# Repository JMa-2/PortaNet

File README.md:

# ***PortaNet Guide***
---
## *TABLE OF CONTENTS*
- [Introduction](#introduction)
- [Hardware](#hardware)
    - [Hardware General](#hardware-general)
    - [Hardware Tools](#hardware-tools)
    - [Schematic](#schematic)
    - [PCB Layout](#pcb-layout)
    - [BOM](#bom)
- [Software](#software)
    - [Software General](#software-general)
    - [Software Tools](#software-tools)
    - [Architecture](#architecture)
    - [Building](#building--flashing)
- [How to Use](#how-to-use)
    - [Use General](#use-general)
    - [PuTTy](#putty)
    - [Console Commands](#console-commands)
<br>
<br>
<br>

## *INTRODUCTION*
The PortaNet is a wifi access point (AP) using the Espressif ESP32-C3FH4 microcontroller. The PortaNet holds the shape and connection types of a typical USB stick. The AP's settings can be modified via a serial console. At this point PuTTy is the only tested terminal emulator software for use with PortaNet.

<br>

<br>
<br>
<br>

## *HARDWARE*
### Hardware General
The critical component consists of the [Espressif ESP32-C3FH4](https://www.espressif.com/en/products/socs/esp32-c3). The ESP32-C3FH4 microcontroller is a ESP32-C3 variant with 4MB internal flash. Simply buying the "normal" ESP32-C3 variant will not suffice due to the lack of internal flash.

The design utilizes a 50 &Omega; impedance, 2.4 GHz wifi antenna. Antennas such as [this](https://www.amazon.com/gp/product/B07D1Z3W7T/ref=ppx_yo_dt_b_search_asin_title?ie=UTF8&psc=1) and [this](https://www.amazon.com/gp/product/B0991PKTDL/ref=ppx_yo_dt_b_search_asin_title?ie=UTF8&psc=1) have worked successfully. There is an unused &pi;-matching circuit that could aid in supporting other antennas.

### Hardware Tools
KiCad v6 was utilized as the EDA tool. The KiCad project can be found in the [hardware directory](hardware/kicad/PortaNet/). Additionally my [KiCad Library](http://192.168.1.19:3000/JMa/KiCad_Library) may contain needed symbols and footprints that the project references.

### Schematic
The current schematic can be seen [here](hardware/kicad/PortaNet_SCH.pdf). 

On page 2 of the schematic, the only oddity worth explaining is the NC of C2. Having C2 installed results in the GPIO9 (pin 15) being pulled low. Resulting in the firmware getting stuck in the bootloader.

On page 3 of the schematic, lives the unused &pi;-matching circuit labeled `Antenna`. If the &pi;-matching circuit does not want to be used, then `L1` should be shorted with a 0 &Omega; resistor.

On page 3 also lives the `Crystal` section. While the load capacitors are labeled 7pF, 8pF caps work with no issues thus far. 

### PCB Layout
The board layout consists of 4 layers, with components on both the top and bottom layers. 

The layer structure consists of the top layer being a signal layer, the second and third layer being GND layers, and the bottom layer being a PWR/signal layer. The top layer or layer 1 of the board is structured to isolate noise sources from other hardware sections. The sub-circuits on the top layer are split into PWR/USB, microcontroller (uC), crystal (XTAL), and radio frequency (RF) sections. GND traces with vias surround the RF and XTAL sections of the top layer.

### BOM
The BOM can be found [here](hardware/kicad/PortaNet/PortaNet.csv). As well as a copy and paste is below. It is again important to note that **the ESP32-C3 part purchased must be a part that contains internal flash.**

| Ref               | Qnty | Value            | Cmp name         | Footprint                                                       |
|-------------------|------|------------------|------------------|-----------------------------------------------------------------|
| C1,               | 1    | 1uF              | C_Small          | Capacitor_SMD:C_0603_1608Metric                                 |
| C2,               | 1    | NC               | C_Small          | Capacitor_SMD:C_0603_1608Metric                                 |
| C3, C7, C13,      | 3    | 0.1uF            | C_Small          | Capacitor_SMD:C_0603_1608Metric                                 |
| C4, C8, C10, C14, | 4    | 10uF             | C_Small          | Capacitor_SMD:C_0603_1608Metric                                 |
| C5, C6,           | 2    | TBD              | C_Small          | Capacitor_SMD:C_0603_1608Metric                                 |
| C9,               | 1    | .1uF             | C_Small          | Capacitor_SMD:C_0603_1608Metric                                 |
| C11, C12,         | 2    | 7pF              | C_Small          | Capacitor_SMD:C_0603_1608Metric                                 |
| D1,               | 1    | DSS13UTR         | D_Schottky       | Diode_SMD:D_SOD-123F                                            |
| J1,               | 1    | SMA              | Conn_Coaxial     | Connector_Coaxial:SMA_Amphenol_132134_Vertical                  |
| J2,               | 1    | Molex 0480370001 | USB_A            | JoesFootprints:Molex_0480370001                                 |
| L1,               | 1    | TBD              | L                | Inductor_SMD:L_0805_2012Metric_Pad1.15x1.40mm_HandSolder        |
| R1, R2, R3,       | 3    | 10k              | R_Small_US       | Resistor_SMD:R_0805_2012Metric                                  |
| R4, R5,           | 2    | 22               | R_Small_US       | Resistor_SMD:R_0805_2012Metric                                  |
| SW1,              | 1    | 434133025816     | SW_SPST          | Button_Switch_SMD:SW_Push_1P1T_NO_Vertical_Wuerth_434133025816  |
| U1,               | 1    | ESP32-C3         | ESP32-C3         | Package_DFN_QFN:QFN-32-1EP_5x5mm_P0.5mm_EP3.3x3.3mm_ThermalVias |
| U2,               | 1    | AP2114HA-3.3TRG1 | AP2114HA-3.3TRG1 | Package_TO_SOT_SMD:SOT-223-3_TabPin2                            |
| Y1,               | 1    | FL400WFQA1       | Crystal_GND24    | Crystal:Crystal_SMD_3225-4Pin_3.2x2.5mm                         |

<br>
<br>
<br>

## *SOFTWARE*
### Software General
The firmware is written in C using [Espressif's IOT Development Framework (ESP-IDF)](https://www.espressif.com/en/products/sdks/esp-idf#:~:text=ESP%2DIDF%20is%20Espressif's%20official,as%20C%20and%20C%2B%2B.). The software utilizes [FreeRTOS](https://www.freertos.org/) as part of the ESP-IDF as well. 

### Software Tools
The software used `ESP-IDF v5.0-dev-3032-g7e71c0cff2-dirty`. The ESP-IDF can be found [here](https://github.com/espressif/esp-idf).

### Architecture
The software utilizes an RTOS variation of [A JcM Architecture](http://192.168.1.19:3000/JMa/JcmArch). Architecture formats can be seen [here](firmware/)

Two threads exists in the software. The first thread, which has the highest priority, is the `Access Point Thread`. The second thread, which has a lower priority compared to the `Access Point Thread`, is the `Console Thread`. The `Access Point Thread` is controlling the wifi soft-AP and the `Console Thread` is controlling the serial console processes that make requests to the `Access Point Interface`. 

### Building & Flashing
1. Clone the repo<br>
`git clone http://192.168.1.19:3000/JMa/PortaNet.git`

2. Enter the firmware folder<br>
`cd PortaNet/firmware/PortaNet/`

3. Source the ESP-IDF export script from proper location<br>
example: `. ~/esp-idf/export.sh`

4. Ensure the target is set to the ESP32-C3<br>
`idf.py set-target esp32c3`

5. Build the project<br>
`idf.py build`

6. Flash the device<br>
`idf.py -p PORT flash`

<br>

If issues arise, Espressif has good documentation located [here](https://docs.espressif.com/projects/esp-idf/en/latest/esp32c3/get-started/linux-macos-setup.html).

<br>
<br>
<br>

## *HOW TO USE*
### Use General
Since the device uses USB 2.0, the operating voltage is 5V. Typical PC USB receptacles work just fine and even phone/device charging bricks should work without issue. The device draws less that 100mA so there shouldn't be power rating issues to monitor.

### PuTTy
At this point, PuTTy is the only terminal emulator that the device has really been tested with. PicoCom, the linux utility, appears to work as well.

PuTTy can be downloaded from [here](https://www.putty.org/) and it is widely used enough to easily find tutorials via Google or Youtube. 

### Console Commands
`help`<br>
Print the list of registered commands.

`status`<br>
Status of the AP which includes info such as the SSID, password, max number of connections, and wifi channel.

`reset`<br>
Reset the AP to its default credentials

`on`<br>
Turn on the AP.

`off`<br>
Turn off the AP.

`devices`<br>
Show info on currently connected devices.

`ssid <NAME>`<br>
Request new SSID of AP.

`password <PW>`<br>
Request new password of AP.

`maxconn <#>`<br>
Request new number of max connection of the AP.

`restart`<br>
Request the AP to restart.

`version`<br>
Request the current software version.

`channel <#>`<br>
Request new wifi channel of the AP.

<br>
<br>
<br>

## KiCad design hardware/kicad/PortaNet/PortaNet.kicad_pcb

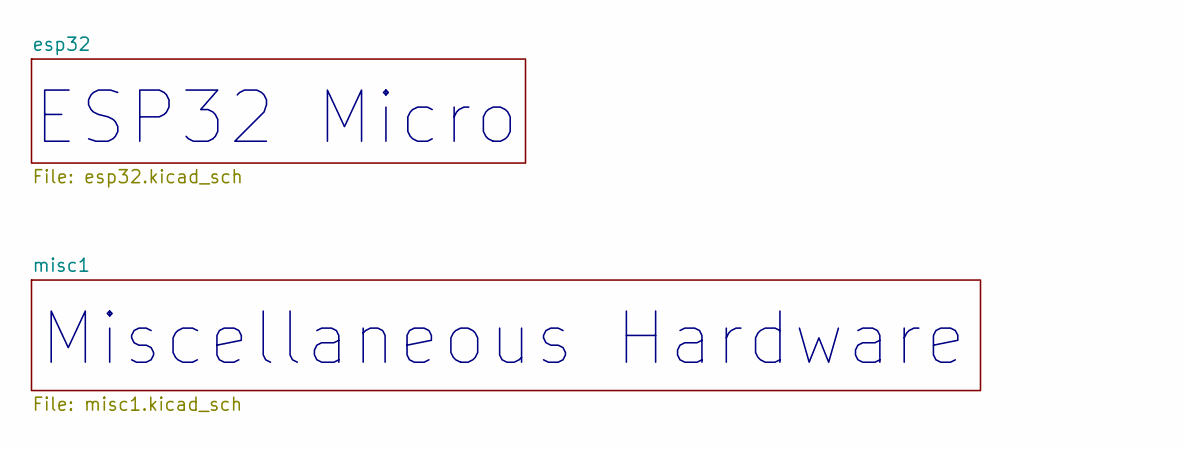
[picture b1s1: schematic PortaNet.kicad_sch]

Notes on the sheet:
Miscellaneous Hardware
ESP32 Micro

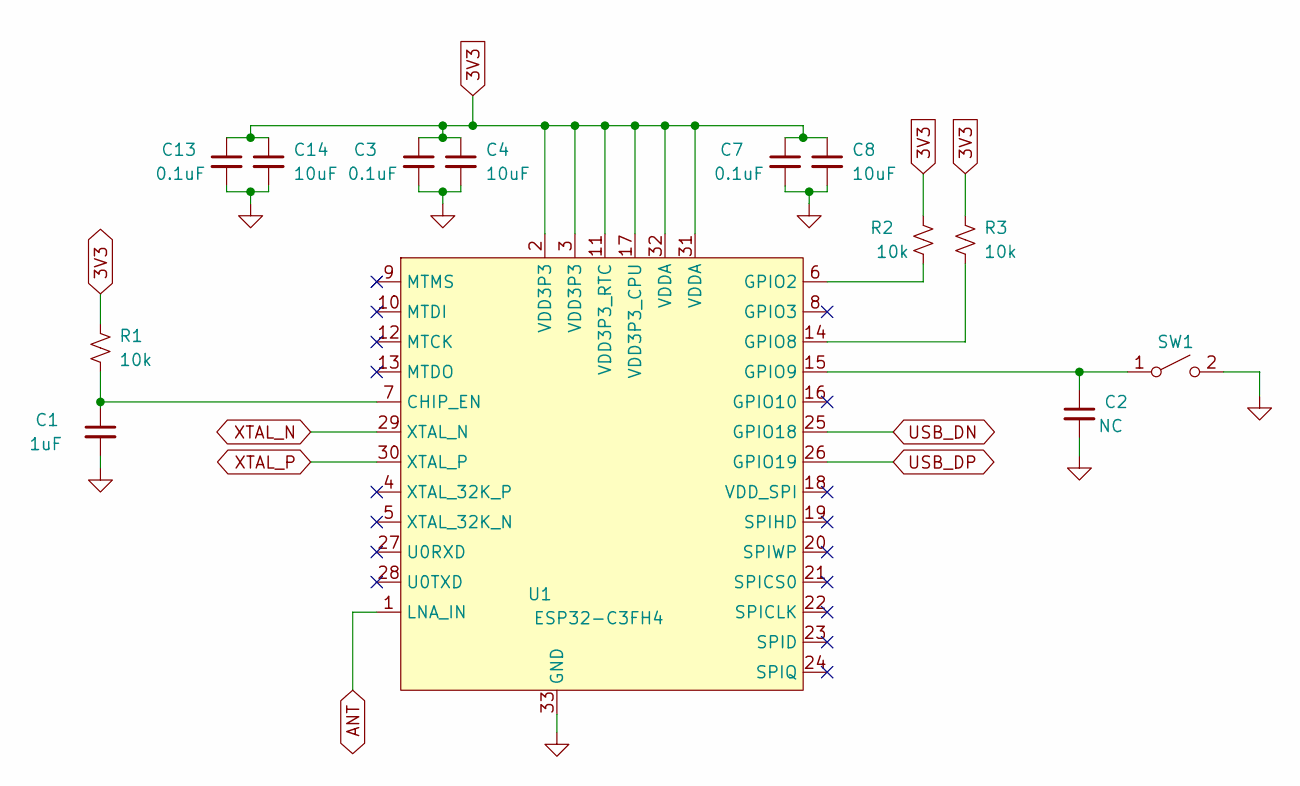
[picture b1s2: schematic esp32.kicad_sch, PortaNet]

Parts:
C1: 1uF; C_0603_1608Metric
C2: NC; C_0603_1608Metric
C3, C7, C13: 0.1uF; C_0603_1608Metric
C4, C8, C14: 10uF; C_0603_1608Metric
R1, R2, R3: 10k; R_0805_2012Metric
SW1: 434133025816; SW_Push_1P1T_NO_Vertical_Wuerth_434133025816
U1: ESP32-C3FH4; QFN-32-1EP_5x5mm_P0.5mm_EP3.3x3.3mm_ThermalVias

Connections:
3V3: C3.1, C4.1, C7.1, C8.1, C13.1, C14.1, R1.2, R2.2, R3.2, U1.2 (VDD3P3), U1.3 (VDD3P3), U1.11 (VDD3P3_RTC), U1.17 (VDD3P3_CPU), U1.31 (VDDA), U1.32 (VDDA); also elsewhere on the board
ANT: U1.1 (LNA_IN); also elsewhere on the board
GND: C1.2, C2.2, C3.2, C4.2, C7.2, C8.2, C13.2, C14.2, SW1.2 (B), U1.33 (GND); also elsewhere on the board
unnamed: C1.1, R1.1, U1.7 (CHIP_EN)
unnamed: C2.1, SW1.1 (A), U1.15 (GPIO9)
unnamed: R3.1, U1.14 (GPIO8)
unnamed: R2.1, U1.6 (GPIO2)
USB_DN: U1.25 (GPIO18); also elsewhere on the board
USB_DP: U1.26 (GPIO19); also elsewhere on the board
XTAL_N: U1.29 (XTAL_N); also elsewhere on the board
XTAL_P: U1.30 (XTAL_P); also elsewhere on the board

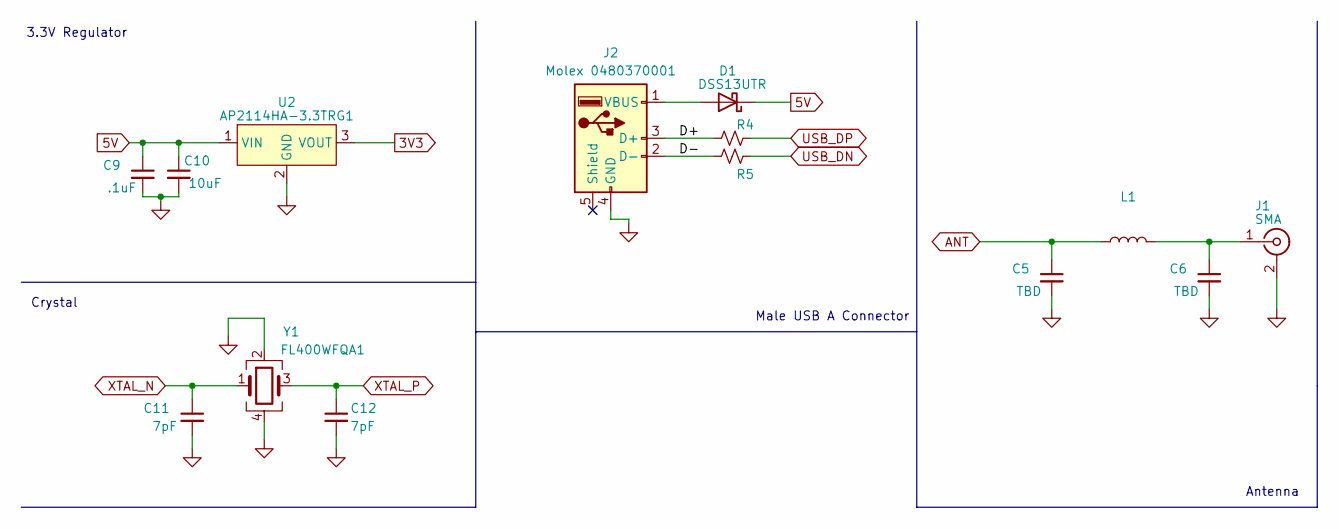
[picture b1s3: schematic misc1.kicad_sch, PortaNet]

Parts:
C5, C6: TBD; C_0603_1608Metric
C9: .1uF; C_0603_1608Metric
C10: 10uF; C_0603_1608Metric
C11, C12: 7pF; C_0603_1608Metric
D1: DSS13UTR; D_SOD-123F
J1: SMA
J2: Molex 0480370001; Molex_0480370001
L1: (no value)
R4, R5: (no value)
U2: AP2114HA-3.3TRG1; SOT-223-3_TabPin2
Y1: FL400WFQA1; Crystal_SMD_3225-4Pin_3.2x2.5mm

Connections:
3V3: U2.3 (VOUT); also elsewhere on the board
5V: C9.1, C10.1, D1.1 (K), U2.1 (VIN)
/misc1/D+: J2.3 (D+), R4.2
/misc1/D-: J2.2 (D-), R5.2
ANT: C5.1, L1.1; also elsewhere on the board
GND: C5.2, C6.2, C9.2, C10.2, C11.2, C12.2, J1.2 (Ext), J2.4 (GND), U2.2 (GND), Y1.2, Y1.4; also elsewhere on the board
unnamed: C6.1, J1.1 (In), L1.2
unnamed: D1.2 (A), J2.1 (VBUS)
USB_DN: R5.1; also elsewhere on the board
USB_DP: R4.1; also elsewhere on the board
XTAL_N: C11.1, Y1.1; also elsewhere on the board
XTAL_P: C12.1, Y1.3; also elsewhere on the board

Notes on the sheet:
Male USB A Connector
3.3V Regulator
Antenna
Crystal

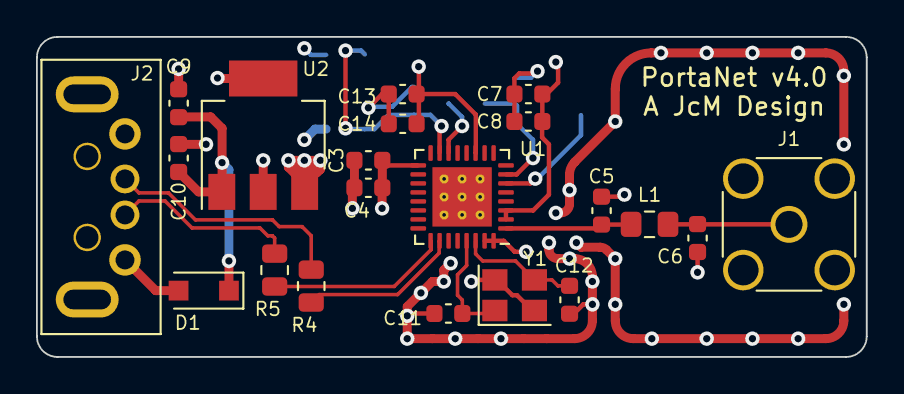
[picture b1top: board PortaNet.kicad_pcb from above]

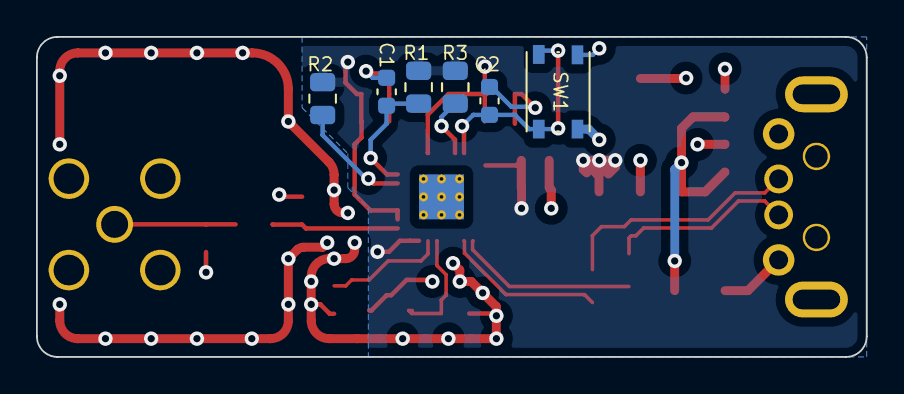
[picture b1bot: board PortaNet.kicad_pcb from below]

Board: 4 copper layers, 46.1 x 17.8 mm, 27 parts (6 on the bottom side), 16 nets.

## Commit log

2022-03-08 init commit
2022-03-08 update sch
2022-03-08 add notes
2022-03-09 eod commit
2022-03-12 first layout rev
2022-03-12 add bom
2022-03-12 add gerbers
2022-03-19 firmware testing
2022-03-19 software notes
2022-03-20 UML architecture init commit
2022-03-20 started firmware
2022-03-22 work on apcontroller
2022-03-22 test gitignore
2022-03-22 modify flash driver and apcontroller
2022-03-23 ap boots up now
2022-03-23 wifi working
2022-03-23 change ssid working
2022-03-23 testing flash num conn bug
2022-03-23 wifi hopefully fulling working now
2022-03-23 eod and i forgot the changes
2022-03-25 kicad cache
2022-03-25 new branch
2022-03-26 board v2 changes
2022-03-26 gerbers v2
2022-03-27 backup catch up
2022-04-04 backup catchup
2022-04-07 adds
2022-04-30 simplify
2022-05-02 gerbers
2022-05-17 backups
2022-05-22 change serial output settings
2022-05-22 start adding console
2022-05-23 console updates
2022-05-23 console progress
2022-05-28 more working commands
2022-05-28 more commands working
2022-05-29 all* commands implemented
2022-05-30 pretty much done with firmware
2022-06-01 more cleanup
2022-06-05 front page readme work
2022-06-05 architecture editing
2022-06-05 more doc updates
2022-06-05 LO draw multi save test
2022-06-05 remove arch pdf
2022-06-05 re-add arch pdf
2022-06-05 testing...
2022-06-05 front page readme updates
2022-06-05 more readme updates
2022-06-05 first complete pass on readme
2022-06-05 minor typos
2022-06-06 software rev output
2022-06-06 update arch with sw version driver
2022-06-06 modifiable wifi channel
2022-06-17 update readme and readme.pdf created
